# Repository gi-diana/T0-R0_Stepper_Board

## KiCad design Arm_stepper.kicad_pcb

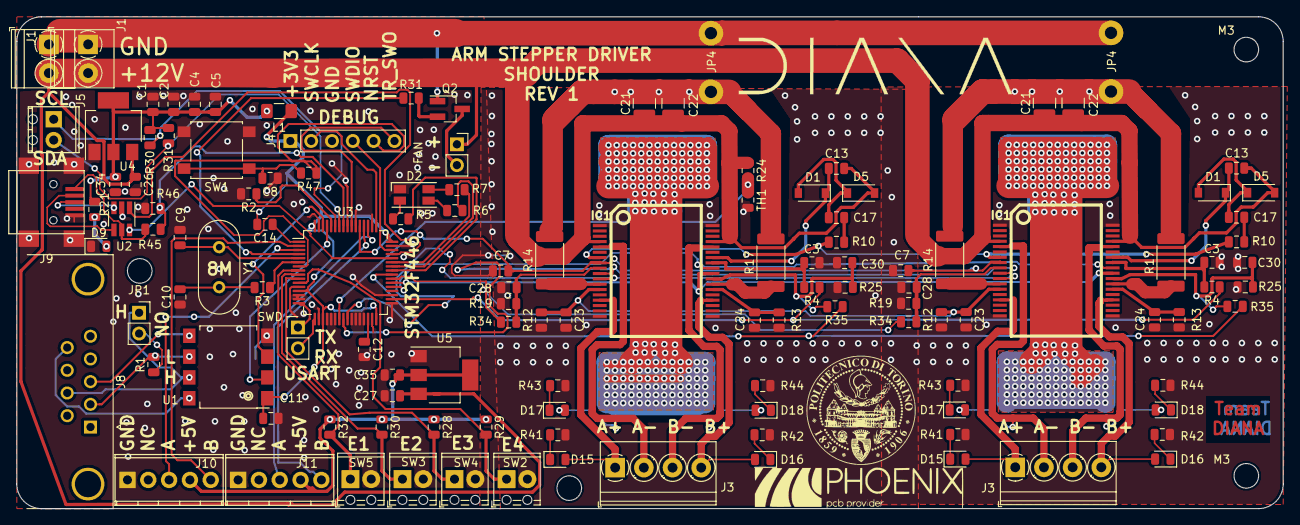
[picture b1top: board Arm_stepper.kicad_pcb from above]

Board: 2 copper layers, 154.5 x 60.0 mm, 127 parts (0 on the bottom side), 80 nets.

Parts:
C1, C2, C4, C5, C7, C7#2, C26, C27, C34, C35: 100nF; C_0805_2012Metric
C3, C3#2: 5.6n; C_0805_2012Metric
C8, C14: 100n; C_0805_2012Metric
C9, C10: 20pF; C_0805_2012Metric
C11, C12: 2.2uF; C_0805_2012Metric
C13, C13#2: 220nF1; C_0805_2012Metric
C17, C17#2: 10nF; C_0805_2012Metric
C21, C21#2: 100nF; C_1210_3225Metric
C22, C22#2: 100uF ceramic; C_1210_3225Metric
C23, C23#2, C24, C24#2: 1nF; C_0805_2012Metric
C28, C28#2, C30, C30#2: 68nF; C_0805_2012Metric
D1, D1#2, D5, D5#2: 1N4148; D_SOD-123
D2: LED_CRGB; LED_RGB_1210
D9: LED_RED; LED_0805_2012Metric
D15, D15#2, D16, D16#2, D17, D17#2, D18, D18#2: LED; LED_0805_2012Metric
FAN: Fan; PinSocket_1x02_P2.54mm_Vertical
IC1, IC1#2: L6208D; POWERSO36
J1, J1#2: 12V_CONN; TerminalBlock_Phoenix_PT-1,5-2-3.5-H_1x02_P3.50mm_Horizontal
J3, J3#2: M1_CONN; TerminalBlock_Phoenix_PT-1,5-4-3.5-H_1x04_P3.50mm_Horizontal
J4: Conn_01x06_Male; PinHeader_1x06_P2.54mm_Vertical
J5: I2C_CONN; TerminalBlock_Phoenix_MPT-2.54mm_2pol
J8: Conn_01x04_Female; DSUB-9_Female_Horizontal_P2.77x2.84mm_EdgePinOffset4.94mm_H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
J9: USB_B_Mini; USB_Mini-B
J10: ENCODER1; TerminalBlock_Phoenix_MPT-2.54mm_5pol
J11: ENCODER2; TerminalBlock_Phoenix_MPT-2.54mm_5pol
JP1: Jumper_NO_Small; PinSocket_1x02_P2.54mm_Vertical
JP4, JP4#2: SolderJumper_2_Bridged; WireConnection_1.50mmDrill
L1: L; L_1206_3216Metric_Pad1.42x1.75mm_HandSolder
M3, M3#2: MountingHole_3mm
Q2: 2N2219; SOT-23_Handsoldering
R1: 120; R_0805_2012Metric
R2, R5, R6, R7, R28, R29, R30#2, R32: 10k; R_0805_2012Metric
R3, R21, R30, R31: 1k; R_0805_2012Metric
R4, R4#2: 100k; R_0805_2012Metric
R10, R10#2: 100; R_0805_2012Metric
R12, R12#2, R13, R13#2: 39k; R_0805_2012Metric
R14, R14#2, R17, R17#2: 0.3; R_2512_6332Metric
R19, R19#2, R25, R25#2: 2.2K; R_0805_2012Metric
R24: 27K; R_0805_2012Metric
R31#2: 70k; R_0805_2012Metric
R34, R34#2, R35, R35#2: 4.7K; R_0805_2012Metric
R41, R41#2, R42, R42#2, R43, R43#2, R44, R44#2: 10K; R_0805_2012Metric
R45: 47K; R_0805_2012Metric
R46: 68K; R_0805_2012Metric
R47: 220; R_0805_2012Metric
SW1: SW_Push_Dual; SW_SPST_B3S-1000
SW2: endstop4; TerminalBlock_Phoenix_MPT-0,5-2-2.54_1x02_P2.54mm_Horizontal
SW3: endstop1; TerminalBlock_Phoenix_MPT-0,5-2-2.54_1x02_P2.54mm_Horizontal
SW4: endstop3; TerminalBlock_Phoenix_MPT-0,5-2-2.54_1x02_P2.54mm_Horizontal
SW5: endstop2; TerminalBlock_Phoenix_MPT-0,5-2-2.54_1x02_P2.54mm_Horizontal
SWD: Pin_Header_Straight_1x02_Pitch2.54mm
TH1: 10k+30T; R_0805_2012Metric
U1: ISO1050-00_isolation; SSO-8_6.7x9.8mm_P2.54mm_Clearance8mm
U2: USBLC6-2SC6; SOT-23-6_Handsoldering
U3: STM32F446RETx; LQFP-64_10x10mm_P0.5mm
U4: LM1117-3.3; SOT-223-3_TabPin2
U5: LM1117-5; SOT-223-3_TabPin2
Y1: 8Mhz; Crystal_HC49-4H_Vertical

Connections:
+3V3: C1.2, C2.2, C4.2, C5.2, C11.1, C14.2, C34.1, J4.1, L1.1, L1.2, R21.2, R30.2, R31.2, U1.1, U3.13, U3.19, U3.32, U3.48, U3.64, U4.2
+5V: C35.1, J10.4, J11.4, R28.1, R29.1, R30#2.1, R32.1, U5.2
+12V: C13.1, C13#2.1, C21.1, C21#2.1, C22.1, C22#2.1, C26.1, C27.1, D5.2, D5#2.2, FAN.1, IC1.4, IC1.33, IC1#2.4, IC1#2.33, J1.2, J1#2.2, R24.1, U4.3, U5.3
/+5v_can: J8.9, U1.8
/M2_A+: D15.2, D15#2.2, IC1.15, IC1#2.15, J3.1, J3#2.1
/M2_A-: D17.2, D17#2.2, IC1.5, IC1#2.5, J3.2, J3#2.2
/M2_B+: D16.2, D16#2.2, IC1.22, IC1#2.22, J3.4, J3#2.4
/M2_B-: D18.2, D18#2.2, IC1.32, IC1#2.32, J3.3, J3#2.3
/NRST: J4.5, R47.1, U3.7
/SWCLK: J4.2, U3.49
/SWDIO: J4.4, U3.46
/TRACESWO: J4.6, U3.55
/gnd_can: J8.3, U1.5
CAN_RX: U1.2, U3.61
CAN_TX: U1.3, U3.62
CLK1: IC1.10, IC1#2.10, U3.24
CRTL1: IC1.28, IC1#2.28, U3.37
CW1: IC1.11, IC1#2.11, U3.25
E1: R32.2, SW5.1, U3.8
E1_1: J10.5, U3.2
E1_2: J10.3, U3.3
E2: R30#2.2, SW3.1, U3.9
E2_1: J11.5, U3.52
E2_2: J11.3, U3.51
E3: R28.2, SW4.1, U3.10
E4: R29.2, SW2.1, U3.11
EN1: R4.1, R4#2.1, U3.34
FAN: R31#2.1, U3.4
GNDD: IC1.37, IC1#2.37
GNDPWR: J1.1, J1#2.1, JP4.1, JP4#2.1, Q2.1
GNDS: C1.1, C2.1, C3.2, C3#2.2, C4.1, C5.1, C7.2, C7#2.2, C8.1, C9.2, C10.1, C11.2, C12.2, C21.2, C21#2.2, C22.2, C22#2.2, C23.2, C23#2.2, C24.2, C24#2.2, C26.2, C27.2, C28.1, C28#2.1, C30.1, C30#2.1, C34.2, C35.2, D2.1, D9.1, IC1.1, IC1.18, IC1.19, IC1.36, IC1#2.1, IC1#2.18, IC1#2.19, IC1#2.36, J4.3, J9.5, J9.6, J10.1, J11.1, JP4.2, JP4#2.2, R2.2, R12.1, R12#2.1, R13.1, R13#2.1, R14.2, R14#2.2, R17.2, R17#2.2, R19.1, R19#2.1, R25.1, R25#2.1, R41.1, R41#2.1, R42.1, R42#2.1, R43.1, R43#2.1, R44.1, R44#2.1, R46.2, SW1.2, SW2.2, SW3.2, SW4.2, SW5.2, TH1.2, U1.4, U2.2, U3.12, U3.14, U3.15, U3.18, U3.20, U3.21, U3.22, U3.26, U3.27, U3.28, U3.29, U3.31, U3.33, U3.35, U3.47, U3.50, U3.54, U3.56, U3.63, U4.1, U5.1
HALF1: IC1.27, IC1#2.27, U3.38
I1: SWD.1, U3.16
I2: SWD.2, U3.17
unnamed: C3.1, C3#2.1, IC1.29, IC1#2.29, R4.2, R4#2.2
unnamed: C8.2, R47.2, SW1.1
unnamed: C9.1, U3.5, Y1.1
unnamed: C10.2, R3.2, Y1.2
unnamed: C12.1, U3.30
unnamed: C13.2, C13#2.2, D1.1, D1#2.1, IC1.30, IC1#2.30
unnamed: C14.1, U3.1
unnamed: C17.1, C17#2.1, D1.2, D1#2.2, D5.1, D5#2.1
unnamed: C17.2, C17#2.2, R10.2, R10#2.2
unnamed: C23.1, C23#2.1, IC1.13, IC1#2.13, R12.2, R12#2.2
unnamed: C24.1, C24#2.1, IC1.24, IC1#2.24, R13.2, R13#2.2
unnamed: C28.2, C28#2.2, IC1.9, IC1#2.9, R19.2, R19#2.2, R34.1, R34#2.1
unnamed: C30.2, C30#2.2, IC1.26, IC1#2.26, R25.2, R25#2.2, R35.1, R35#2.1
unnamed: D2.2, R5.1
unnamed: D2.3, R6.1
unnamed: D2.4, R7.1
unnamed: D9.2, R21.1
unnamed: D15.1, D15#2.1, R41.2, R41#2.2
unnamed: D16.1, D16#2.1, R42.2, R42#2.2
unnamed: D17.1, D17#2.1, R43.2, R43#2.2
unnamed: D18.1, D18#2.1, R44.2, R44#2.2
unnamed: IC1.7, IC1#2.7, R10.1, R10#2.1
unnamed: IC1.12, IC1#2.12, R14.1, R14#2.1
unnamed: IC1.25, IC1#2.25, R17.1, R17#2.1
unnamed: J8.7, JP1.1, U1.7
unnamed: J8.2, R1.2, U1.6
unnamed: J9.1, R45.1, U2.5
unnamed: J9.2, U2.4
unnamed: J9.3, U2.3
unnamed: JP1.2, R1.1
unnamed: FAN.2, Q2.3
unnamed: Q2.2, R31#2.2
unnamed: R2.1, U3.60
unnamed: R3.1, U3.6
unnamed: R5.2, U3.41
unnamed: R6.2, U3.42
unnamed: R7.2, U3.43
PWMA1: R34.2, R34#2.2, U3.39
PWMB1: R35.2, R35#2.2, U3.40
RST1: C7.1, C7#2.1, IC1.8, IC1#2.8, U3.53
USB_DM: U2.6, U3.44
USB_DP: U2.1, U3.45
USB_EN: R45.2, R46.1, U3.57
i2C1_SCL: J5.2, R31.1, U3.58
i2C1_SDA: J5.1, R30.1, U3.59
t_SENS: R24.2, TH1.1, U3.23

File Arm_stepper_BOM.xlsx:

Id | Designator | Package | Quantity |  | Designation | Mouser | RS
4 | R35,R34,R34,R35 | R_0805_2012Metric | 4 | 24 | 4.7K | https://www.mouser.it/ProductDetail/Yageo/SR0805FR-474K7L?qs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
5 | R25,R19,R19,R25 | R_0805_2012Metric | 4 | 24 | 2.2K | https://www.mouser.it/ProductDetail/Vishay/CRCW08052K20FKEAC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
6 | R17,R14,R14,R17 | R_2512_6332Metric | 4 | 24 | 0.3 | https://www.mouser.it/ProductDetail/Bourns/CRM2512-FX-R300EL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
7 | R13,R12,R12,R13 | R_0805_2012Metric | 4 | 24 | 39k | https://www.mouser.it/ProductDetail/Panasonic/ERJ-P06D3902V?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
8 | R10,R10 | R_0805_2012Metric | 2 | 12 | 100 | https://www.mouser.it/ProductDetail/Bourns/CRS0805AFX-1000EL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
9 | R4,R4 | R_0805_2012Metric | 2 | 12 | 100k | https://www.mouser.it/ProductDetail/Vishay/CRCW0805100KFKEAC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
10 | J3,J3 | TerminalBlock_Phoenix_PT-1,5-4-3.5-H_1x04_P3.50mm_Horizontal | 2 | 12 | M1_CONN | https://www.mouser.it/ProductDetail/Phoenix-Contact/1862068?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
11 | IC1,IC1 | POWERSO36 | 2 | 12 | L6208D | https://www.mouser.it/ProductDetail/STMicroelectronics/L6208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
12 | D18,D17,D16,D15,D15,D16,D17,D18 | LED_0805_2012Metric | 8 | 48 | LED | https://www.mouser.it/ProductDetail/Dialight/599-0120-007F?q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
13 | D5,D1,D1,D5 | D_SOD-123 | 4 | 24 | 1N4148 | https://www.mouser.it/ProductDetail/Diodes-Incorporated/1N41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
14 | C30,C28,C28,C30 | C_0805_2012Metric | 4 | 24 | 68nF | https://www.mouser.it/ProductDetail/KEMET/C0805X682K5RAC7800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
15 | C24,C23,C23,C24 | C_0805_2012Metric | 4 | 24 | 1nF | https://www.mouser.it/ProductDetail/KEMET/C0805C102J2GECAUTO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
16 | C17,C17 | C_0805_2012Metric | 2 | 12 | 10nF | https://www.mouser.it/ProductDetail/KEMET/C0805X103K5RAC7210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
17 | C13,C13 | C_0805_2012Metric | 2 | 12 | 220nF | https://www.mouser.it/ProductDetail/AVX/08055C224K4T4A?qs=sG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
18 | C7,C1,C2,C4,C5,C7,C26,C27,C34,C35,C14 | C_0805_2012Metric | 11 | 66 | 100nF | https://www.mouser.it/ProductDetail/KEMET/C0805C104K1RECAUTO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
19 | C3,C3 | C_0805_2012Metric | 2 | 12 | 5.6nF | https://www.mouser.it/ProductDetail/KEMET/C0805C561J1GACAUTO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
20 | C22,C22 | C_1210_3225Metric | 2 | 12 | 100uF ceramic | https://www.mouser.it/ProductDetail/Taiyo-Yuden/EMK325ABJ107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
21 | C21,C21 | C_1210_3225Metric | 2 | 12 | 100nF | https://www.mouser.it/ProductDetail/KEMET/C1210X104K2RACAUTO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
22 | J5 | TerminalBlock_Phoenix_MPT-2.54mm_2pol | 1 | 6 | I2C_CONN | https://www.mouser.it/ProductDetail/Phoenix-Contact/1725656?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
23 | C9,C10 | C_0805_2012Metric | 2 | 12 | 20pF | https://www.mouser.it/ProductDetail/AVX/08055A200F4T2A?qs=sG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
24 | C11,C12 | C_0805_2012Metric | 2 | 12 | 2.2uF | https://www.mouser.it/ProductDetail/Wurth-Electronics/885012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
26 | D2 | LED_RGB_1210 | 1 | 6 | LED_CRGB | https://www.mouser.it/ProductDetail/Inolux/IN-S128TATRGB?qs=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
27 | D9 | LED_0805_2012Metric | 1 | 6 | LED_RED | https://www.mouser.it/ProductDetail/Dialight/599-0120-007F?q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
28 | J1 | TerminalBlock_Phoenix_PT-1,5-2-3.5-H_1x02_P3.50mm_Horizontal | 1 | 6 | 12V_CONN | https://www.mouser.it/ProductDetail/TE-Connectivity/1-283401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
29 | J4 | PinHeader_1x06_P2.54mm_Vertical | 1 | 6 | Conn_01x06_Male
30 | J8 | DSUB-9_Female_Horizontal_P2.77x2.84mm_EdgePinOffset4.94mm_Housed_MountingHolesO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 | 1 | 6 | Conn_01x04_Female | https://www.mouser.it/ProductDetail/TE-Connectivity-AMP/2301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
31 | J9 | USB_Micro-B_Molex-105017-0001 | 1 | 6 | USB_B_Mini | https://www.mouser.it/ProductDetail/Molex/47589-0001?qs=sGAE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
32 | J10 | TerminalBlock_Phoenix_MPT-0,5-4-2.54_1x04_P2.54mm_Horizontal | 1 | 6 | ENCODER1
33 | J11 | TerminalBlock_Phoenix_MPT-0,5-4-2.54_1x04_P2.54mm_Horizontal | 1 | 6 | ENCODER2
34 | JP1 | PinSocket_1x02_P2.54mm_Vertical | 1 | 6 | Jumper_NO_Small
35 | L1 | L_1206_3216Metric_Pad1.42x1.75mm_HandSolder | 1 | 6 | L | https://www.mouser.it/ProductDetail/TDK/HF30ACC321611-TD25?q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
36 | FAN | PinSocket_1x02_P2.54mm_Vertical | 1 | 6 | Fan
37 | Q2 | SOT-23_Handsoldering | 1 | 6 | 2N2219 | https://www.mouser.it/ProductDetail/Nexperia/PMST2222115?qs=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
38 | R1 | R_0805_2012Metric | 1 | 6 | 120 | https://www.mouser.it/ProductDetail/Vishay/CRCW1206120RFKEAC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
39 | R2,R5,R6,R7,R28,R29,R30,R32, R44,R43,R42,R41,R41,R42,R43,R44 | R_0805_2012Metric | 16 | 96 | 10k | https://www.mouser.it/ProductDetail/Vishay/CRCW120610K0FKEAC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
40 | R3,R21 | R_0805_2012Metric | 2 | 12 | 1k | https://www.mouser.it/ProductDetail/Vishay/CRCW12061K00FKEAC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
41 | R24 | R_0805_2012Metric | 1 | 6 | 27K | https://www.mouser.it/ProductDetail/Yageo/AC1206FR-07316KL?q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
42 | R31 | R_0805_2012Metric | 1 | 6 | 70k | https://www.mouser.it/ProductDetail/Panasonic/ERJ-8ENF6982V?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
43 | R45 | R_0805_2012Metric | 1 | 6 | 47K | https://www.mouser.it/ProductDetail/Vishay/CRCW120647K0FKEAC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
44 | R46 | R_0805_2012Metric | 1 | 6 | 68K | https://www.mouser.it/ProductDetail/Bourns/CR1206-FX-6802ELF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
45 | R47 | R_0805_2012Metric | 1 | 6 | 220 | https://www.mouser.it/ProductDetail/Vishay/CRCW1206220RFKEAC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
46 | SW1 | SW_SPST_B3S-1000 | 1 | 6 | SW_Push_Dual | https://www.mouser.it/ProductDetail/Omron-Electronics/B3S-10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
47 | SW2 | TerminalBlock_Phoenix_MPT-0,5-2-2.54_1x02_P2.54mm_Horizontal | 4 | 24 | endstop4 | https://www.mouser.it/ProductDetail/Phoenix-Contact/1725656?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
48 | SW3 | TerminalBlock_Phoenix_MPT-0,5-2-2.54_1x02_P2.54mm_Horizontal |  | 0 | endstop1
49 | SW4 | TerminalBlock_Phoenix_MPT-0,5-2-2.54_1x02_P2.54mm_Horizontal |  | 0 | endstop3
50 | SW5 | TerminalBlock_Phoenix_MPT-0,5-2-2.54_1x02_P2.54mm_Horizontal |  | 0 | endstop2
51 | TH1 | R_0805_2012Metric | 1 | 6 | 10k+30T | https://www.mouser.it/ProductDetail/TDK/NTCG203NH103JTDS?qs=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
52 | U1 | SSO-8_6.7x9.8mm_P2.54mm_Clearance8mm | 1 | 6 | ISO1050-00_isolation | https://www.mouser.it/ProductDetail/Texas-Instruments/ISO105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
53 | U2 | SOT-23-6_Handsoldering | 1 | 6 | USBLC6-2SC6 | https://www.mouser.it/ProductDetail/STMicroelectronics/USBLC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
54 | U3 | LQFP-64_10x10mm_P0.5mm | 1 | 6 | STM32F446RETx | https://www.mouser.it/ProductDetail/STMicroelectronics/STM32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
55 | U4 | SOT-223-3_TabPin2 | 1 | 6 | LM1117-3.3 | https://www.mouser.it/ProductDetail/Texas-Instruments/LM1117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
56 | U5 | SOT-223-3_TabPin2 | 1 | 6 | LM1117-5 | https://www.mouser.it/ProductDetail/Texas-Instruments/LM1117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
57 | Y1 | Crystal_HC49-4H_Vertical | 1 | 6 | 8Mhz | https://www.mouser.it/ProductDetail/Citizen-FineDevice/HC-49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
 | numero schede | 6

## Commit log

2018-12-21 first
2018-12-21 relocating schematics
2018-12-22 pcb design init
2018-12-23 mcu circuitry drawn
2018-12-23 pcb design almost complete
2018-12-25 copper completed
2018-12-26 copper compl1
2018-12-26 schematic update
2019-01-01 fixes
2019-01-09 little fix
2019-02-25 improve
2019-02-26 init
2019-02-27 work
2019-03-01 dual
2019-03-01 duala
2019-03-01 finish
2019-03-01 finish2
2019-03-01 finish3
2019-03-02 finish4
2019-03-02 finish 3d
2019-03-08 finished
2019-03-13 gerber
2019-03-22 final version
